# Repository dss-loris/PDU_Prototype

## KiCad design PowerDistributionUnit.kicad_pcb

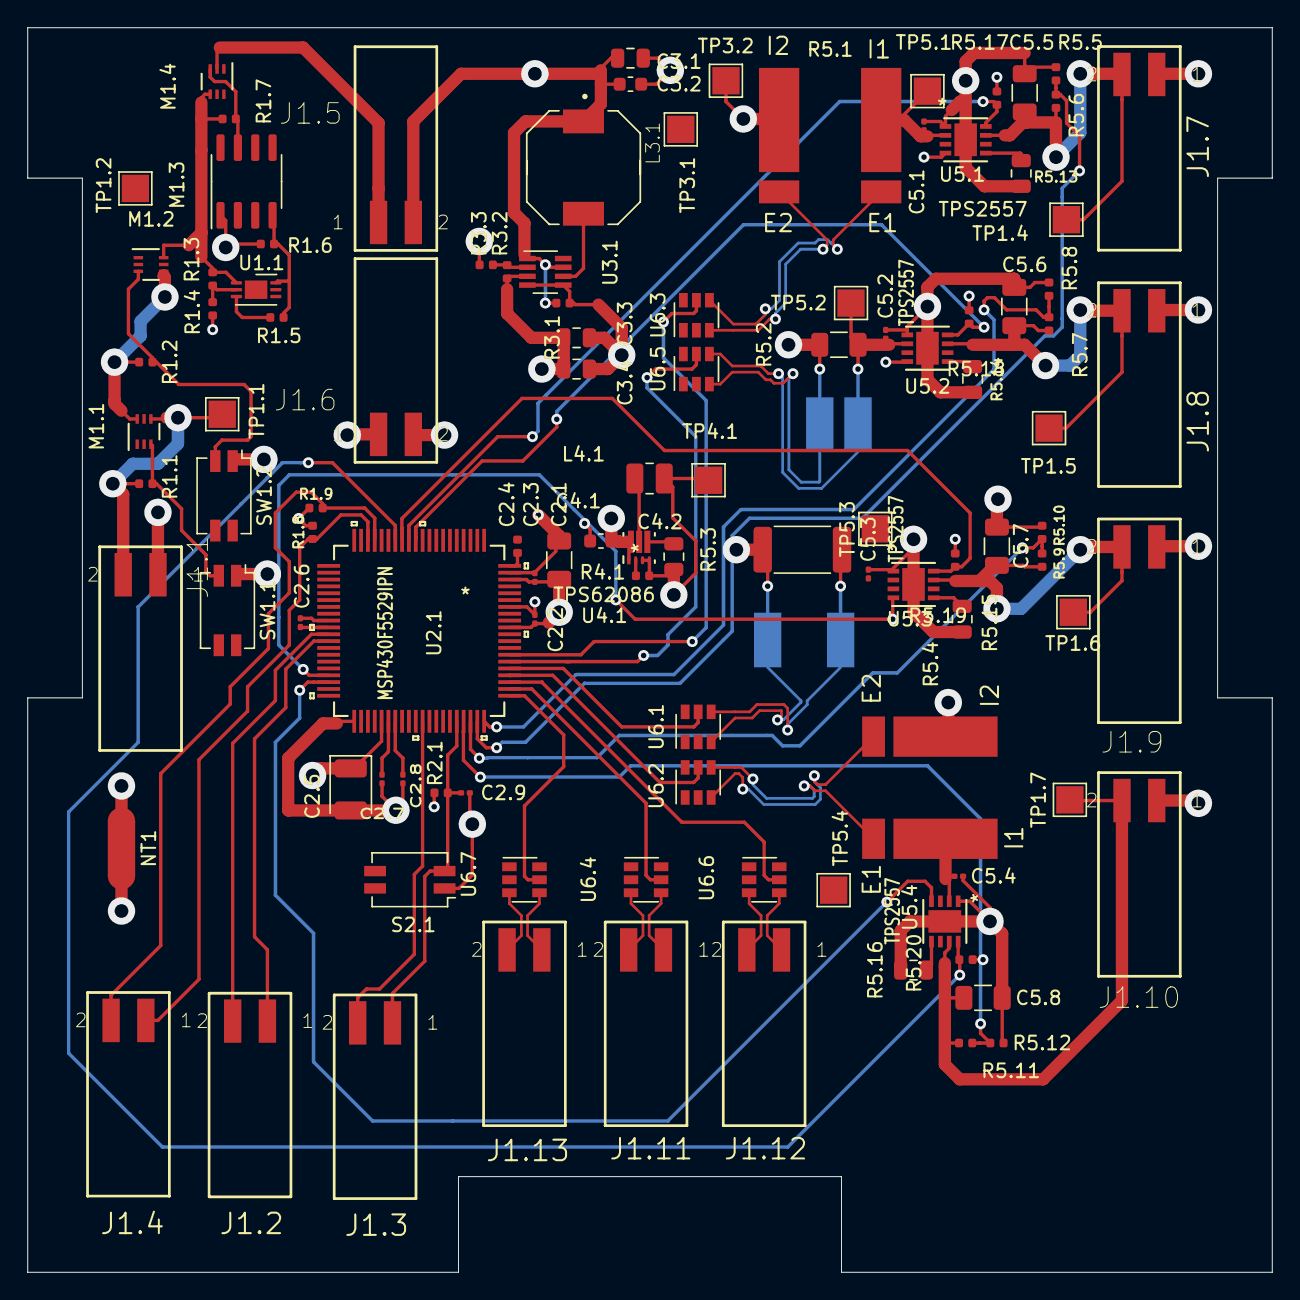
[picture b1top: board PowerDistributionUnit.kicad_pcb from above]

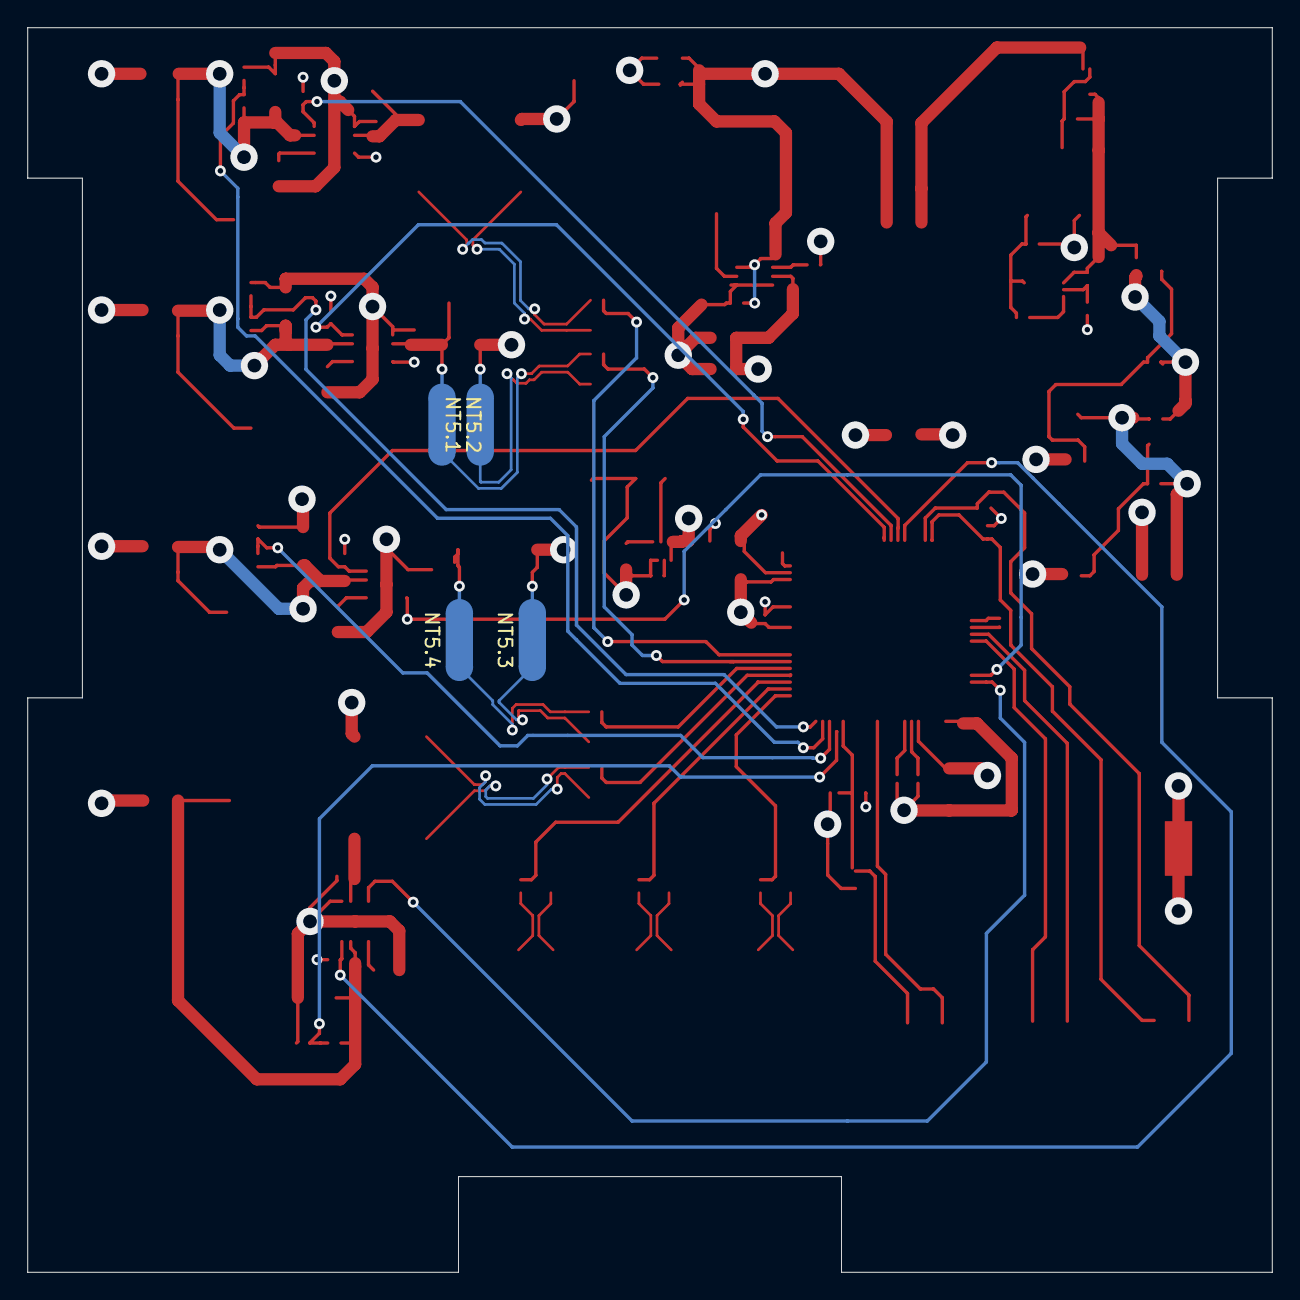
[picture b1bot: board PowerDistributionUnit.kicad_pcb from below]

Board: 4 copper layers, 91.0 x 91.0 mm, 112 parts (4 on the bottom side), 66 nets.

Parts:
C2.1: 10u; C_1206_3216Metric
C2.2, C2.3, C2.6: 100n; C_0201_0603Metric
C2.4: 470n; C_0402_1005Metric
C2.5: 4.7u; CP_EIA-3528-12_Kemet-T
C2.7, C2.8: 220n; C_0201_0603Metric
C2.9: 1n; C_0201_0603Metric
C3.1, C3.3, C3.4: 22u; C_0805_2012Metric
C3.2: 1u; C_0603_1608Metric
C4.1: 10uF; C_0603_1608Metric
C4.2: 22uF; C_0805_2012Metric
C5.1, C5.2, C5.3, C5.4: 0.1u; C_0201_0603Metric
C5.5, C5.6, C5.7, C5.8: 150u; C_1206_3216Metric
J1.1: POWER_PINS; SAMTEC-TSM-102-01-X-SH
J1.2: UART_PINS; SAMTEC-TSM-102-01-X-SH
J1.3: SBW_PINS; SAMTEC-TSM-102-01-X-SH
J1.4: I2C_PINS; SAMTEC-TSM-102-01-X-SH
J1.5: 30_Minute_Bypass_Jumpers; SAMTEC-TSM-102-01-X-SH
J1.6: Direct_Power_Pins; SAMTEC-TSM-102-01-X-SH
J1.7: OBC_PINS; SAMTEC-TSM-102-01-X-SH
J1.8: PL_PINS; SAMTEC-TSM-102-01-X-SH
J1.9: ACS_PINS; SAMTEC-TSM-102-01-X-SH
J1.10: RF_PINS; SAMTEC-TSM-102-01-X-SH
J1.11: EPS_PINS; SAMTEC-TSM-102-01-X-SH
J1.12: I_BAT_PINS; SAMTEC-TSM-102-01-X-SH
J1.13: I_PV_PINS; SAMTEC-TSM-102-01-X-SH
L3.1: 1.5u; IND_1217AS-H-1R5N=P3
L4.1: 0.47uH; L_1008_2520Metric
M1.1, M1.2, M1.4: PMOS; DFN-6-1EP_2x2mm_P0.5mm_EP0.61x1.42mm
M1.3: NMOS; SOIC-8_3.9x4.9mm_P1.27mm
NT1, NT5.1, NT5.2, NT5.3, NT5.4: Net-Tie_2; NetTie-2_SMD_Pad2.0mm
R1.1, R1.2, R1.6, R1.7, R3.1, R3.3, R5.5, R5.6, R5.7, R5.8, R5.9, R5.10, R5.11, R5.12, R5.17, R5.18, R5.19, R5.20: 100k; R_0402_1005Metric
R1.3, R4.1: 1M; R_0402_1005Metric
R1.4: 887k; R_0402_1005Metric
R1.5: 86.6k; R_0402_1005Metric
R1.8, R1.9: 4.7k; R_0402_1005Metric
R2.1: 47k; R_0402_1005Metric
R3.2: 909k; R_0402_1005Metric
R5.1, R5.4: 3.57m; VISHAY_SENSE_R
R5.2: 14.7m; R_1206_3216Metric
R5.3: 22.9m; R_2512_6332Metric
R5.13, R5.14, R5.15, R5.16: 20k; R_0805_2012Metric
S2.1: RST; SW_DIP_SPSTx02_Slide_Copal_CHS-02A_W5.08mm_P1.27mm_JPin
SW1.1, SW1.2: Inhibit; SW_DIP_SPSTx02_Slide_Copal_CHS-02A_W5.08mm_P1.27mm_JPin
TP1.1: SW1_TP; TestPoint_Pad_2.0x2.0mm
TP1.2: SW2_TP; TestPoint_Pad_2.0x2.0mm
TP1.4: OBC_TP; TestPoint_Pad_2.0x2.0mm
TP1.5: PL_TP; TestPoint_Pad_2.0x2.0mm
TP1.6: ACS_TP; TestPoint_Pad_2.0x2.0mm
TP1.7: RF_TP; TestPoint_Pad_2.0x2.0mm
TP3.1: Unreggulated_TP; TestPoint_Pad_2.0x2.0mm
TP3.2: 5v_TP; TestPoint_Pad_2.0x2.0mm
TP4.1: 3.3V_TP; TestPoint_Pad_2.0x2.0mm
TP5.1: OBC_LS_TP; TestPoint_Pad_2.0x2.0mm
TP5.2: PL_LS_TP; TestPoint_Pad_2.0x2.0mm
TP5.3: ACS_LS_TP; TestPoint_Pad_2.0x2.0mm
TP5.4: RF_LS_TP; TestPoint_Pad_2.0x2.0mm
U1.1: LTC6995; DFN-6-1EP_3x2mm_P0.5mm_EP1.65x1.35mm
U2.1: MSP430F5529IPN; MSP430F5529IPNR
U3.1: RT4812; TSOT-23-8
U4.1: TPS62086; TPS62086RLTR
U5.1, U5.2, U5.3, U5.4: TPS2557; TPS2557DRBR
U6.1, U6.2, U6.3, U6.4, U6.5, U6.6, U6.7: MAX44284E; SOT-23-6

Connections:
/3.3V_Regulated: C2.1.1 (DVCC1), C2.2.1, C2.3.1 (DVCC1), C4.2.1, L4.1.2, R1.8.2, R1.9.2, R4.1.1, TP4.1.1, U2.1.11 (AVCC1), U2.1.18 (DVCC1), U6.1.1, U6.2.1, U6.3.1, U6.4.1, U6.5.1, U6.6.1, U6.7.1
/5V_Regulated: C2.5.1 (VBUS), C3.3.1, C3.4.1, NT5.1.2, NT5.3.2, R3.2.1, R5.1.4, R5.2.1, R5.3.1, R5.4.4, R5.17.1, R5.18.1, R5.19.1, R5.20.1, TP3.2.1, U2.1.65 (VBUS)
/30_Minute_Output: J1.5.1, M1.4.2 (D), R3.1.1
/ACS+: NT5.3.1, U6.1.3
/ACS-: NT5.4.1, U6.1.4
/Current Sensing/EPS+: J1.11.2, U6.4.3
/Current Sensing/EPS-: J1.11.1, U6.4.4, U6.4.6
/Current Sensing/Ibat+: J1.12.2, U6.6.3
/Current Sensing/Ibat-: J1.12.1, U6.6.4
/Current Sensing/Ipv+: J1.13.2, U6.7.3
/Current Sensing/Ipv-: J1.13.1, U6.7.4
/I_ACS: U2.1.5, U6.1.5
/I_EPS: U2.1.2, U6.4.5
/I_OBC: U2.1.7, U6.3.5
/I_PL: U2.1.6, U6.5.5
/I_RF: U2.1.4, U6.2.5
/OBC+: R5.1.2, U6.3.3
/OBC-: R5.1.1, U6.3.4
/PL+: NT5.1.1, U6.5.3
/PL-: NT5.2.1, U6.5.4
/Power_MSP430/3.0_SDA_I2C: J1.4.2, R1.9.1, U2.1.37
/Power_MSP430/3.1_SCL_I2C: J1.4.1, R1.8.1, U2.1.38
/Power_MSP430/4.4_UART_TXD: J1.2.2, U2.1.51
/Power_MSP430/4.5_UART_RXD: J1.2.1, U2.1.52
/Power_MSP430/SBWCLK: J1.3.2, U2.1.71
/Power_MSP430/SBWTDIO: C2.9.1, J1.3.1, R2.1.2, S2.1.2, U2.1.76 (RST)
/RF+: R5.4.2, U6.2.3
/RF-: R5.4.1, U6.2.4
/SubsystemLoadSwitches/ACS: C5.7.1, J1.9.2, R5.9.1, TP1.6.1, U5.3.7
/SubsystemLoadSwitches/OBC: C5.5.1, J1.7.2, R5.5.1, TP1.4.1, U5.1.7
/SubsystemLoadSwitches/PL: C5.6.1, J1.8.2, R5.7.1, TP1.5.1, U5.2.7
/SubsystemLoadSwitches/RF: C5.8.1, J1.10.2, R5.11.1, TP1.7.1, U5.4.7
/V_ACS: R5.9.2, R5.10.1, U2.1.78
/V_OBC: R5.5.2, R5.6.1, U2.1.79
/V_PL: R5.7.2, R5.8.1, U2.1.80
/V_RF: R5.11.2, R5.12.1, U2.1.77
/enable_ACS: U2.1.57, U5.3.4
/enable_OBC: U2.1.9, U5.1.4
/enable_PL: U2.1.8, U5.2.4
/enable_RF: U2.1.58, U5.4.4
/fault_ACS: R5.19.2, U2.1.33, U5.3.8
/fault_OBC: R5.17.2, U2.1.32, U5.1.8
/fault_PL: R5.18.2, U2.1.31, U5.2.8
/fault_RF: R5.20.2, U2.1.34, U5.4.8
GNDA: C2.2.2, C3.1.2, C3.2.2, C3.3.2, C3.4.2, C4.1.2, C4.2.2, C5.1.2, C5.2.2, C5.3.2, C5.4.2, C5.5.2, C5.6.2, C5.7.2, C5.8.2, J1.1.1, J1.6.2, J1.7.1, J1.8.1, J1.9.1, J1.10.1, M1.3.1 (S), NT1.1, R1.4.2, R1.6.2, R3.1.2, R3.3.2, R5.6.2, R5.8.2, R5.10.2, R5.12.2, R5.13.2, R5.14.2, R5.15.2, R5.16.2, SW1.1.1, SW1.2.1, U2.1.14 (AVSS1), U5.1.1, U5.2.1, U5.3.1, U5.4.1, U6.1.2, U6.2.2, U6.3.2, U6.4.2, U6.5.2, U6.6.2, U6.7.2
GNDD: C2.1.2, C2.3.2, C2.5.2, C2.7.2, C2.8.2, C2.9.2, NT1.2, S2.1.1, U2.1.19 (DVSS1), U2.1.61
Ibat_ADC: U2.1.3, U6.6.5
Ipv_ADC: U2.1.1, U6.7.5
unnamed: C5.1.1, R5.1.3, TP5.1.1, U5.1.2
unnamed: C5.2.1, NT5.2.2, R5.2.2, TP5.2.1, U5.2.2
unnamed: C5.3.1, NT5.4.2, R5.3.2, TP5.3.1, U5.3.2
unnamed: C5.4.1, R5.4.3, TP5.4.1, U5.4.2
unnamed: J1.1.2, M1.1.4 (S), R1.1.1, TP1.1.1
unnamed: C3.1.1, C3.2.1, C4.1.1, J1.5.2, J1.6.1, L3.1.1, TP3.1.1, U4.1.1 (EN), U4.1.7 (VIN)
unnamed: M1.1.6 (D), M1.2.4 (S), R1.2.2, TP1.2.1
unnamed: R1.1.2, SW1.1.2
unnamed: M1.2.3 (G), M1.3.7 (D), R1.2.1, R1.7.1, SW1.2.2
unnamed: M1.2.6 (D), M1.4.4 (S), R1.3.1, U1.1.1 (V+)
unnamed: M1.3.4 (G), R1.5.1, R1.6.1, U1.1.6 (OUT)
unnamed: R1.3.2, R1.4.1, U1.1.2 (DIV)
unnamed: R1.5.2, U1.1.3 (SET)
unnamed: R3.2.2, R3.3.1
unnamed: R5.13.1, U5.1.5
unnamed: R5.14.1, U5.2.5
unnamed: R5.15.1, U5.3.5
unnamed: R5.16.1, U5.4.5

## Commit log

2020-02-14 Updated PDU schematic, Inhibit switches and 30 minute time
2020-04-25 updated PDU schematic with footprints
2020-05-06 made the footprints relative paths
2020-07-06 Near complete Pcbnew file for the PDU PCB. All signal routes are complete, need to add ground and power via's to some ICs and a general review. Also need to add print screen to label the different se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
2020-08-01 Adjusted power plane and added missing ground VIAs
2020-09-21 Changed board outline to reflect CubeSat dimensions

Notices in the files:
parts and their libraries:
Copyright 2016 Accelerated Designs. All rights reserved.
